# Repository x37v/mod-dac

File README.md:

# MOD-DAC

An 8 channel DAC Schematic/PCB project intended for modular use.
It should be able to give -5..5 or 0..5 or some other range within that.
It is intended to be driven by 3.3v signals from a micro controller, not included in this project.

This project is adapted from the [Mutable Instruments "Stages"](https://mutable-instruments.net/modules/stages/open_source/).
Thank you to [O. Gillet](https://mutable-instruments.net).

## License

<br /><span xmlns:dct="http://purl.org/dc/terms/" property="dct:title">MOD-DAC</span> by <a xmlns:cc="http://creativecommons.org/ns#" href="https://github.com/x37v/mod-dac" property="cc:attributionName" rel="cc:attributionURL">Alex Norman</a> is licensed under a <a rel="license" href="http://creativecommons.org/licenses/by-sa/4.0/">Creative Commons Attribution-ShareAlike 4.0 International License</a>.<br />Based on a work at <a xmlns:dct="http://purl.org/dc/terms/" href="https://mutable-instruments.net/modules/stages/open_source/" rel="dct:source">https://mutable-instruments.net/modules/stages/open_source/</a>.

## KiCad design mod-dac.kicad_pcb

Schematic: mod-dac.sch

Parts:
C13, C17, C18, C19, C20, C21, C22: 22u; C_0805_2012Metric_Pad1.33x1.40mm_HandSolder
C14, C15, C16: 1u; C_0805_2012Metric_Pad1.33x1.40mm_HandSolder
J1: digi in; PinHeader_1x04_P2.54mm_Vertical
J2: cv out; PinHeader_1x09_P2.54mm_Vertical
L1, L2, L3: BEAD; L_0603_1608Metric_Pad1.05x0.95mm_HandSolder
P1: MTA-156-4
TR1: VREF TRIM; trimmer
TR2: BIAS TRIM; trimmer
U4: DAC8168; TSSOP-14_4.4x5mm_P0.65mm
U5: LD2981; SOT-89-3_Handsoldering

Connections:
+15V: C18.1, C21.1, L2.1; also elsewhere on the board
-15V: C17.2, C22.2, L1.1; also elsewhere on the board
DIN: J1.2, U4.13
GND: C13.2, C14.2, C15.2, C16.2, C17.1, C18.2, C19.2, C20.2, C21.2, C22.1, J1.4, J2.9, P1.2, P1.3, TR1.3, TR2.3, U4.12, U5.2; also elsewhere on the board
unnamed: C19.1, L3.2, U5.3
unnamed: L1.2, P1.4
unnamed: L2.2, L3.1, P1.1
REFVCC: C13.1, C14.1, C20.1, TR1.1, TR2.1, U4.2, U5.1
SCLK: J1.1, U4.14
\SYNC: J1.3, U4.1
dac0: U4.3; also elsewhere on the board
dac1: U4.11; also elsewhere on the board
dac2: U4.4; also elsewhere on the board
dac3: U4.10; also elsewhere on the board
dac4: U4.5; also elsewhere on the board
dac5: U4.9; also elsewhere on the board
dac6: U4.6; also elsewhere on the board
dac7: U4.8; also elsewhere on the board
vbias: C16.1, TR2.2; also elsewhere on the board
vout0: J2.1; also elsewhere on the board
vout1: J2.2; also elsewhere on the board
vout2: J2.3; also elsewhere on the board
vout3: J2.4; also elsewhere on the board
vout4: J2.5; also elsewhere on the board
vout5: J2.6; also elsewhere on the board
vout6: J2.7; also elsewhere on the board
vout7: J2.8; also elsewhere on the board
vref: C15.1, TR1.2, U4.7

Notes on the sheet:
do we want a separate vreg for the reference voltages?

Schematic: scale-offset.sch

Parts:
C1, C2, C3, C4, C5, C6, C7, C8: 100p; C_0805_2012Metric_Pad1.33x1.40mm_HandSolder
C9, C10, C11, C12: 100n; C_0805_2012Metric_Pad1.33x1.40mm_HandSolder
R1, R2, R3, R4, R13, R14, R15, R16: 23.7k; R_0805_2012Metric_Pad1.33x1.40mm_HandSolder
R5, R6, R7, R8, R17, R18, R19, R20: 100k; R_0805_2012Metric_Pad1.33x1.40mm_HandSolder
R9, R10, R11, R12, R21, R22, R23, R24: 1k; R_0805_2012Metric_Pad1.33x1.40mm_HandSolder
U1, U2: TL074; TSSOP-14_4.4x5mm_P0.65mm

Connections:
+15V: C9.1, C11.1, U1.4 (V+), U2.4 (V+); also elsewhere on the board
-15V: C10.2, C12.2, U1.11 (V-), U2.11 (V-); also elsewhere on the board
GND: C9.2, C10.1, C11.2, C12.1; also elsewhere on the board
unnamed: C1.1, R9.2, U1.1
unnamed: C1.2, R1.1, R5.2, U1.2 (-)
unnamed: C2.1, R10.2, U1.7
unnamed: C2.2, R2.1, R6.2, U1.6 (-)
unnamed: C3.1, R11.2, U1.8
unnamed: C3.2, R3.1, R7.2, U1.9 (-)
unnamed: C4.1, R12.2, U1.14
unnamed: C4.2, R4.1, R8.2, U1.13 (-)
unnamed: C5.1, R21.2, U2.1
unnamed: C5.2, R13.1, R17.2, U2.2 (-)
unnamed: C6.1, R22.2, U2.7
unnamed: C6.2, R14.1, R18.2, U2.6 (-)
unnamed: C7.1, R23.2, U2.8
unnamed: C7.2, R15.1, R19.2, U2.9 (-)
unnamed: C8.1, R24.2, U2.14
unnamed: C8.2, R16.1, R20.2, U2.13 (-)
dac0: R16.2; also elsewhere on the board
dac1: R1.2; also elsewhere on the board
dac2: R15.2; also elsewhere on the board
dac3: R2.2; also elsewhere on the board
dac4: R14.2; also elsewhere on the board
dac5: R3.2; also elsewhere on the board
dac6: R13.2; also elsewhere on the board
dac7: R4.2; also elsewhere on the board
vbias: U1.3 (+), U1.5 (+), U1.10 (+), U1.12 (+), U2.3 (+), U2.5 (+), U2.10 (+), U2.12 (+); also elsewhere on the board
vout0: R5.1, R9.1; also elsewhere on the board
vout1: R6.1, R10.1; also elsewhere on the board
vout2: R7.1, R11.1; also elsewhere on the board
vout3: R8.1, R12.1; also elsewhere on the board
vout4: R17.1, R21.1; also elsewhere on the board
vout5: R18.1, R22.1; also elsewhere on the board
vout6: R19.1, R23.1; also elsewhere on the board
vout7: R20.1, R24.1; also elsewhere on the board

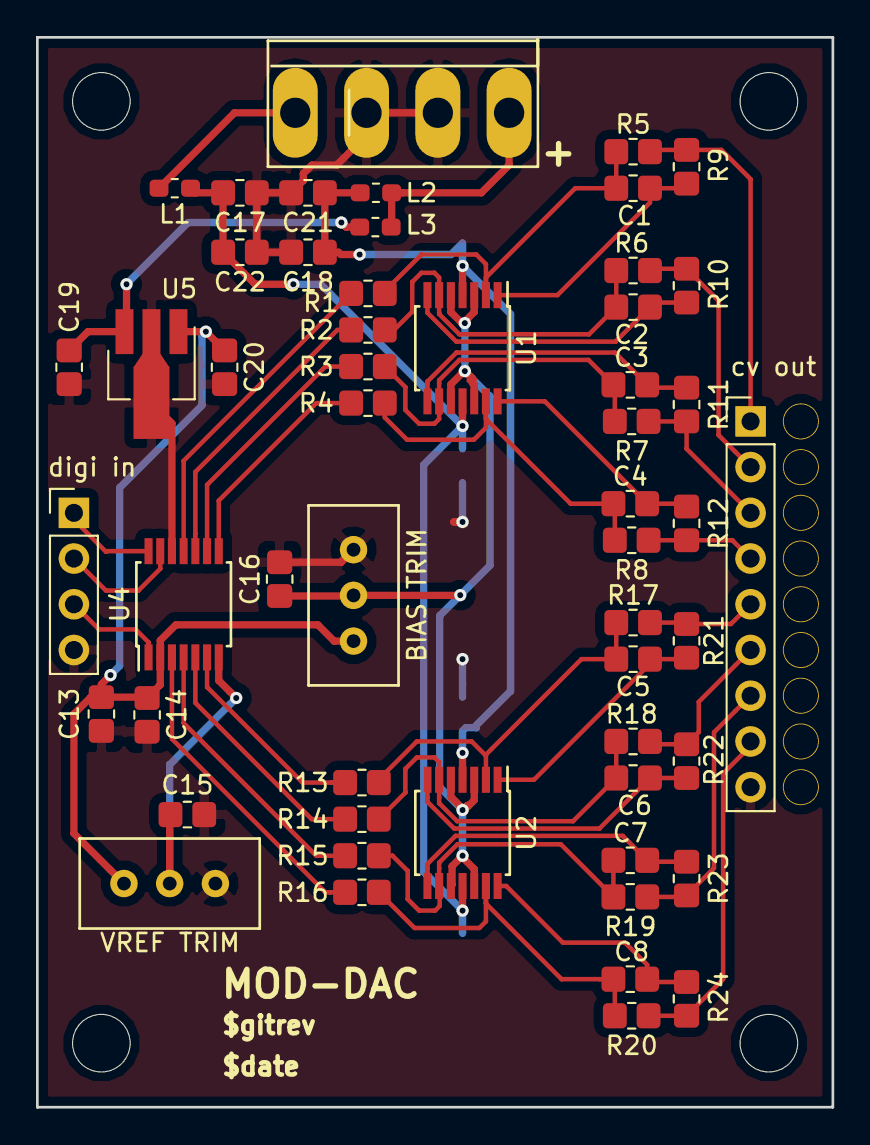
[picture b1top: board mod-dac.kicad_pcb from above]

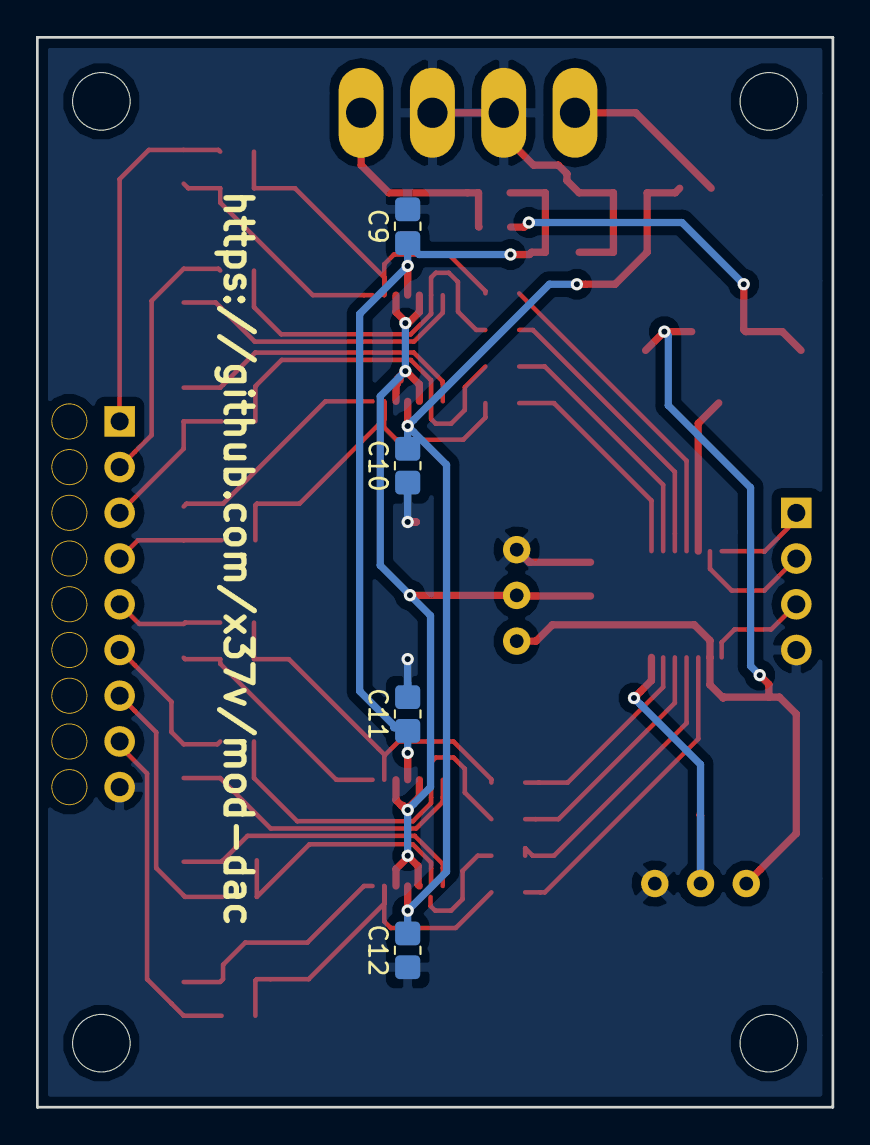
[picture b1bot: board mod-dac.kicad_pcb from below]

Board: 2 copper layers, 44.2 x 59.4 mm, 62 parts (4 on the bottom side), 44 nets.

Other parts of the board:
REF1, REF2, REF3, REF4: MountingHole_3.2mm_M3

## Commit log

2018-12-27 ignore file
2018-12-27 working simulation
2018-12-27 looking like the right values for ~4x gain
2018-12-28 added readme with notes
2018-12-28 added doc
2018-12-28 added tl074 model
2018-12-28 updated with TL074
2018-12-28 cleanup
2018-12-28 major schematic progress
2018-12-29 added 15v power
2018-12-29 moved io around
2018-12-29 fixed up power supply
2018-12-29 corrected cap orientation
2018-12-30 3.3v supply, also.. updated per stages
2018-12-30 license
2018-12-30 share alike
2018-12-30 more notes
2018-12-30 removed polar parts
2018-12-30 no more F
2018-12-30 fixed incorrect chip number, assigned packages
2018-12-30 rough bom
2018-12-30 don't ignore csv..
2018-12-31 really rough layout
2018-12-31 updated routing to more nicely map to chip
2018-12-31 more rough layout work
2018-12-31 reordered connection for digital input
2018-12-31 more routing
2018-12-31 i think i've routed the rest of the non gnd signals
2018-12-31 edge cut
2018-12-31 moved power a bit
2018-12-31 corrected the edge cut
2018-12-31 added strain relief
2018-12-31 all hooked up, have text
2019-01-03 updated text layout
2019-01-03 moved text around
    align output info with pin 1, move githash
